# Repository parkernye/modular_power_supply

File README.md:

# modular_synth_power_supply
Modular Synth Power Supply

This PCB was designed to be the main power supply for a modular synth.
It takes its input voltage from a step down transformer, and converts it into the standard +/-12V and +5V used by all modular synths. 
The output uses the standard 10pin connector, and can interface with the 'Bus Board' to distribute power in the system. 

Future modifications:
-Update silkscreen for better legibility
-Add status LED

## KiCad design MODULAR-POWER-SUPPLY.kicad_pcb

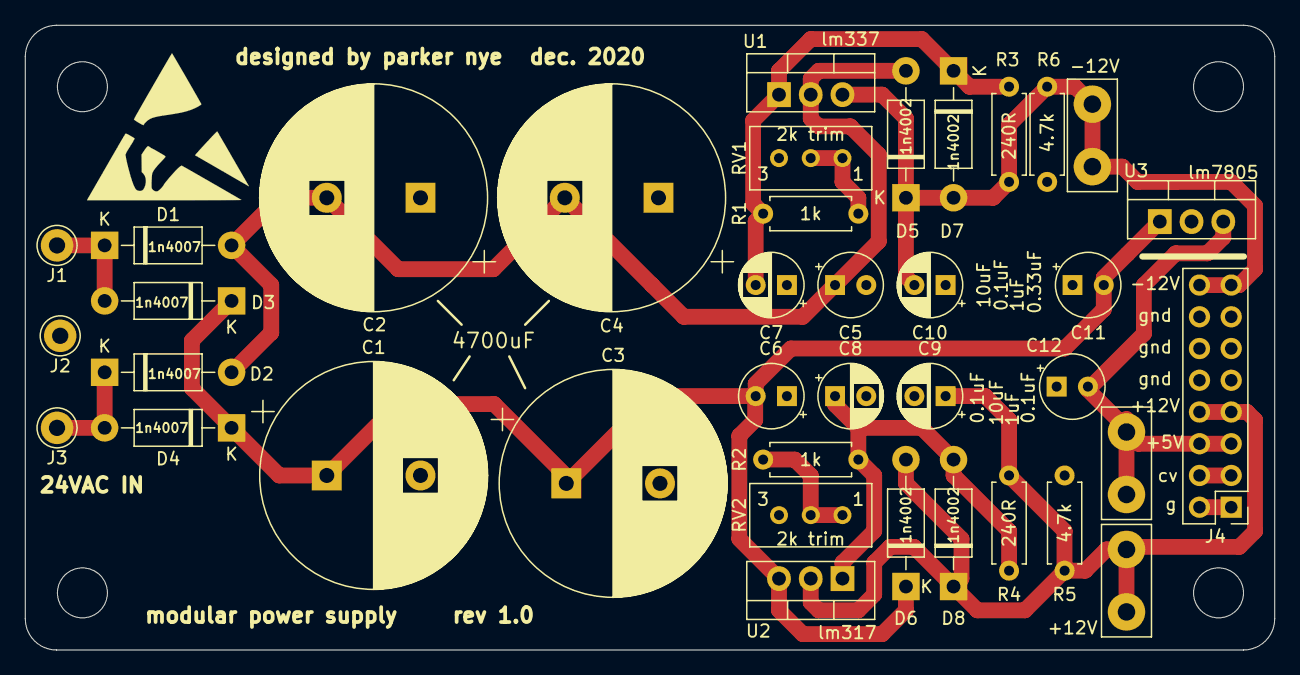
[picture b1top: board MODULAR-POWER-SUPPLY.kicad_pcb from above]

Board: 2 copper layers, 100.0 x 50.0 mm, 42 parts (0 on the bottom side), 14 nets.

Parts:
C1, C2, C3, C4: 4700uF; CP_Radial_D18.0mm_P7.50mm
C5, C6, C12: .1uF; CP_Radial_Tantal_D5.0mm_P2.50mm
C7, C8: 10uF; CP_Radial_D5.0mm_P2.50mm
C9, C10: 1uF; CP_Radial_D5.0mm_P2.50mm
C11: .33uF; CP_Radial_Tantal_D5.0mm_P2.50mm
D1, D2, D3, D4: 1N4007; D_DO-41_SOD81_P10.16mm_Horizontal
D5, D6, D7, D8: 1N4002; D_DO-41_SOD81_P10.16mm_Horizontal
H1, H2, H3, H4: MountingHole; MountingHole_4mm
J1: SEC1_TRANS; Pin_D1.3mm_L11.0mm
J2: GND_TRANS; Pin_D1.3mm_L11.0mm
J3: SEC2_TRANS; Pin_D1.3mm_L11.0mm
J4: Conn_02x08_Odd_Even; PinHeader_2x08_P2.54mm_Vertical
J5, J6, J7: Connector_Generic_Conn_01x02; weldingtab
R1, R2: 1k; R_Axial_DIN0207_L6.3mm_D2.5mm_P7.62mm_Horizontal
R3, R4: 240R; R_Axial_DIN0207_L6.3mm_D2.5mm_P7.62mm_Horizontal
R5, R6: 4.7k; R_Axial_DIN0207_L6.3mm_D2.5mm_P7.62mm_Horizontal
RV1, RV2: 2kTRIM; Potentiometer_Bourns_3296W_Vertical
U1: LM337T_NRND; TO-220-3_Vertical
U2: LM317T; TO-220-3_Vertical
U3: LM7805_TO220; TO-220-3_Vertical

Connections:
+5V: C12.2, J4.5, J4.6, J7.1, J7.2, U3.3
GND: C1.2, C2.1, C3.2, C4.1, C5.2, C6.1, C7.1, C8.2, C9.2, C10.1, C11.1, C12.1, J2.1, J4.9, J4.10, J4.11, J4.12, J4.13, J4.14, R5.2, R6.2, RV1.3, RV2.3, U3.2
unnamed: C1.1, C3.1, C6.2, C11.2, D3.1, D4.1, D6.1, U2.3, U3.1
unnamed: C2.2, C4.2, C5.1, D1.2, D2.2, D5.2, U1.2
unnamed: C7.2, D7.1, R1.1, R3.2, U1.1
unnamed: C8.1, D8.2, R2.1, R4.2, U2.1
unnamed: D1.1, D3.2, J1.1
unnamed: D2.1, D4.2, J3.1
unnamed: J4.1, J4.2
unnamed: J4.3, J4.4
unnamed: R1.2, RV1.1, RV1.2
unnamed: R2.2, RV2.1, RV2.2
VCC: C9.1, D6.2, D8.1, J4.7, J4.8, J5.1, J5.2, R4.1, R5.1, U2.2
VDD: C10.2, D5.1, D7.2, J4.15, J4.16, J6.1, J6.2, R3.1, R6.1, U1.3

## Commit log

2023-11-01 init
